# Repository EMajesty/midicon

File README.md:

# MIDI Controller — MCU Pinout and Wiring Reference

MCU: Arduino Mega 2560 Pro  
Logic voltage: 5 V

## 1. MCU Pin Assignments

| Arduino Pin | Net | Function |
|---|---|---|
| D3 | E1_PB | Encoder 1 push button |
| D5 | E1_A | Encoder 1 channel A |
| D7 | E1_B | Encoder 1 channel B |
| D9 | E2_PB | Encoder 2 push button |
| D11 | E2_A | Encoder 2 channel A |
| D14 | E2_B | Encoder 2 channel B |
| D15 | E3_PB | Encoder 3 push button |
| D17 | E3_A | Encoder 3 channel A |
| D18 | MIDI_OUT | MIDI output (TX1) |
| D19 | MIDI_IN | MIDI input (RX1) |
| D21 | E3_B | Encoder 3 channel B |
| D23 | E4_PB | Encoder 4 push button |
| D24 | C1 | Matrix column 1 |
| D25 | E4_A | Encoder 4 channel A |
| D26 | C2 | Matrix column 2 |
| D27 | E4_B | Encoder 4 channel B |
| D28 | C3 | Matrix column 3 |
| D30 | C4 | Matrix column 4 |
| D32 | LEDS | WS2812B data |
| D33 | F1 | Function button 1 |
| D35 | F2 | Function button 2 |
| D36 | LCD_RS | LCD register select |
| D37 | F3 | Function button 3 |
| D38 | LCD_E | LCD enable |
| D39 | F4 | Function button 4 |
| D40 | LCD_DB4 | LCD data bit 4 |
| D41 | R1 | Matrix row 1 |
| D42 | LCD_DB5 | LCD data bit 5 |
| D43 | R2 | Matrix row 2 |
| D44 | LCD_DB6 | LCD data bit 6 |
| D45 | R3 | Matrix row 3 |
| D46 | LCD_DB7 | LCD data bit 7 |
| D47 | R4 | Matrix row 4 |
| A0 | ADC_F1 | Fader 1 |
| A2 | ADC_F2 | Fader 2 |
| A4 | ADC_F3 | Fader 3 |
| A6 | ADC_F4 | Fader 4 |
| A8 | ADC_J1X | Joystick 1 X |
| A10 | ADC_J1Y | Joystick 1 Y |
| A12 | ADC_J2X | Joystick 2 X |
| A14 | ADC_J2Y | Joystick 2 Y |

D0/D1 are reserved for USB serial debugging.

## 2. Rotary Encoders

Four rotary encoders with integrated push buttons.

| Contact | Connection |
|---|---|
| A | E*_A MCU input |
| B | E*_B MCU input |
| Common | GND |
| Push button terminal 1 | E*_PB MCU input |
| Push button terminal 2 | GND |

- All 12 inputs use `INPUT_PULLUP`.
- Rotary contacts pull their respective inputs LOW when closed.
- Push buttons are active LOW.
- Quadrature decoding and debouncing are handled in firmware.

## 3. Function Buttons

Four independent momentary buttons.

| Contact | Connection |
|---|---|
| Terminal 1 | F1–F4 MCU input |
| Terminal 2 | GND |

- Configure as `INPUT_PULLUP`.
- Pressed = LOW.

## 4. Button Matrix

4×4 matrix with one diode per button.

| Row | C1 (D24) | C2 (D26) | C3 (D28) | C4 (D30) |
|---|---|---|---|---|
| R1 (D41) | SW1 | SW2 | SW3 | SW4 |
| R2 (D43) | SW5 | SW6 | SW7 | SW8 |
| R3 (D45) | SW9 | SW10 | SW11 | SW12 |
| R4 (D47) | SW13 | SW14 | SW15 | SW16 |

### Wiring

Each button is wired:

`Column → Switch → Diode anode → Diode cathode → Row`

- Diode cathode (striped end) faces the row.
- One diode per switch prevents ghosting.
- Columns are configured as `INPUT_PULLUP`.
- Scan by driving one row LOW at a time.
- Inactive rows are high-impedance (`INPUT`).
- A pressed button on the active row reads LOW at its column.

## 5. Analog Controls

Four stereo faders (one track used per fader) and two dual-axis joysticks.

| Control | ADC Pin |
|---|---|
| Fader 1 | A0 |
| Fader 2 | A2 |
| Fader 3 | A4 |
| Fader 4 | A6 |
| Joystick 1 X | A8 |
| Joystick 1 Y | A10 |
| Joystick 2 X | A12 |
| Joystick 2 Y | A14 |

### Wiring

Each potentiometer:

| Terminal | Connection |
|---|---|
| End 1 | +5 V |
| Wiper | ADC input |
| End 3 | GND |

- ADC range: 0–1023.
- Reversing the outer terminals reverses the control direction.
- Unused tracks of stereo faders are left unconnected.
- Joystick axes each use one potentiometer.

## 6. WS2812B LEDs

Four addressable RGB LEDs connected in series.

| Signal | Connection |
|---|---|
| First LED DIN | D32 (LEDS) |
| Each LED DOUT | Next LED DIN |
| All VDD | +5 V |
| All VSS | GND |
| Final LED DOUT | Unconnected |

All LEDs are controlled through one MCU pin.

## 7. LCD

20×2 character LCD, 4-bit parallel interface.

Module markings: Winstar WDH0048-TMI-ET#00 / Forewin 2002AE-1.

The following assumes a standard HD44780-compatible 16-pin interface.

| LCD Pin | Signal | Connection |
|---|---|---|
| 1 | VSS | GND |
| 2 | VDD | +5 V |
| 3 | VO | Contrast potentiometer wiper |
| 4 | RS | D36 |
| 5 | R/W | GND |
| 6 | E | D38 |
| 7–10 | DB0–DB3 | Unconnected |
| 11 | DB4 | D40 |
| 12 | DB5 | D42 |
| 13 | DB6 | D44 |
| 14 | DB7 | D46 |
| 15 | LED+ | +5 V (verify current limiting) |
| 16 | LED− | GND |

### Contrast potentiometer (RV9)

| Terminal | Connection |
|---|---|
| End 1 | +5 V |
| Wiper | LCD VO |
| End 3 | GND |

Firmware initialization:

`LiquidCrystal lcd(36, 38, 40, 42, 44, 46);`

## 8. MIDI Input

5-pin DIN MIDI input using a 6N137 optocoupler.

## 9. MIDI Output

5-pin DIN MIDI output driven by hardware UART1.

Firmware:

`Serial1.begin(31250);`

## 10. Power Supply

9 V DC input regulated to 5 V using an L7805.

| Component | Connection |
|---|---|
| Barrel jack positive | +9 V |
| Barrel jack negative | GND |
| L7805 IN | +9 V |
| L7805 GND | GND |
| L7805 OUT | +5 V |
| C2 | Input decoupling |
| C1 | Output decoupling |

The +5 V rail supplies the MCU, controls, LCD, MIDI circuitry and LEDs.

## Firmware and configurator

The v1 firmware is a standalone, four-page configurable MIDI controller. Build it with `pio run -d firmware`; see [firmware/README.md](firmware/README.md) for operation, EEPROM layout, MIDI conventions, and the USB protocol.

The native Python configurator provides JSON validation/import/export, device upload/download, explicit EEPROM save/reload, and a PySide6 GUI:

```sh
python -m pip install -r requirements.txt
python -m configurator validate config/default.json
python -m configurator gui
```

See [configurator/README.md](configurator/README.md) for all commands and [docs/hardware-test-checklist.md](docs/hardware-test-checklist.md) for physical verification.

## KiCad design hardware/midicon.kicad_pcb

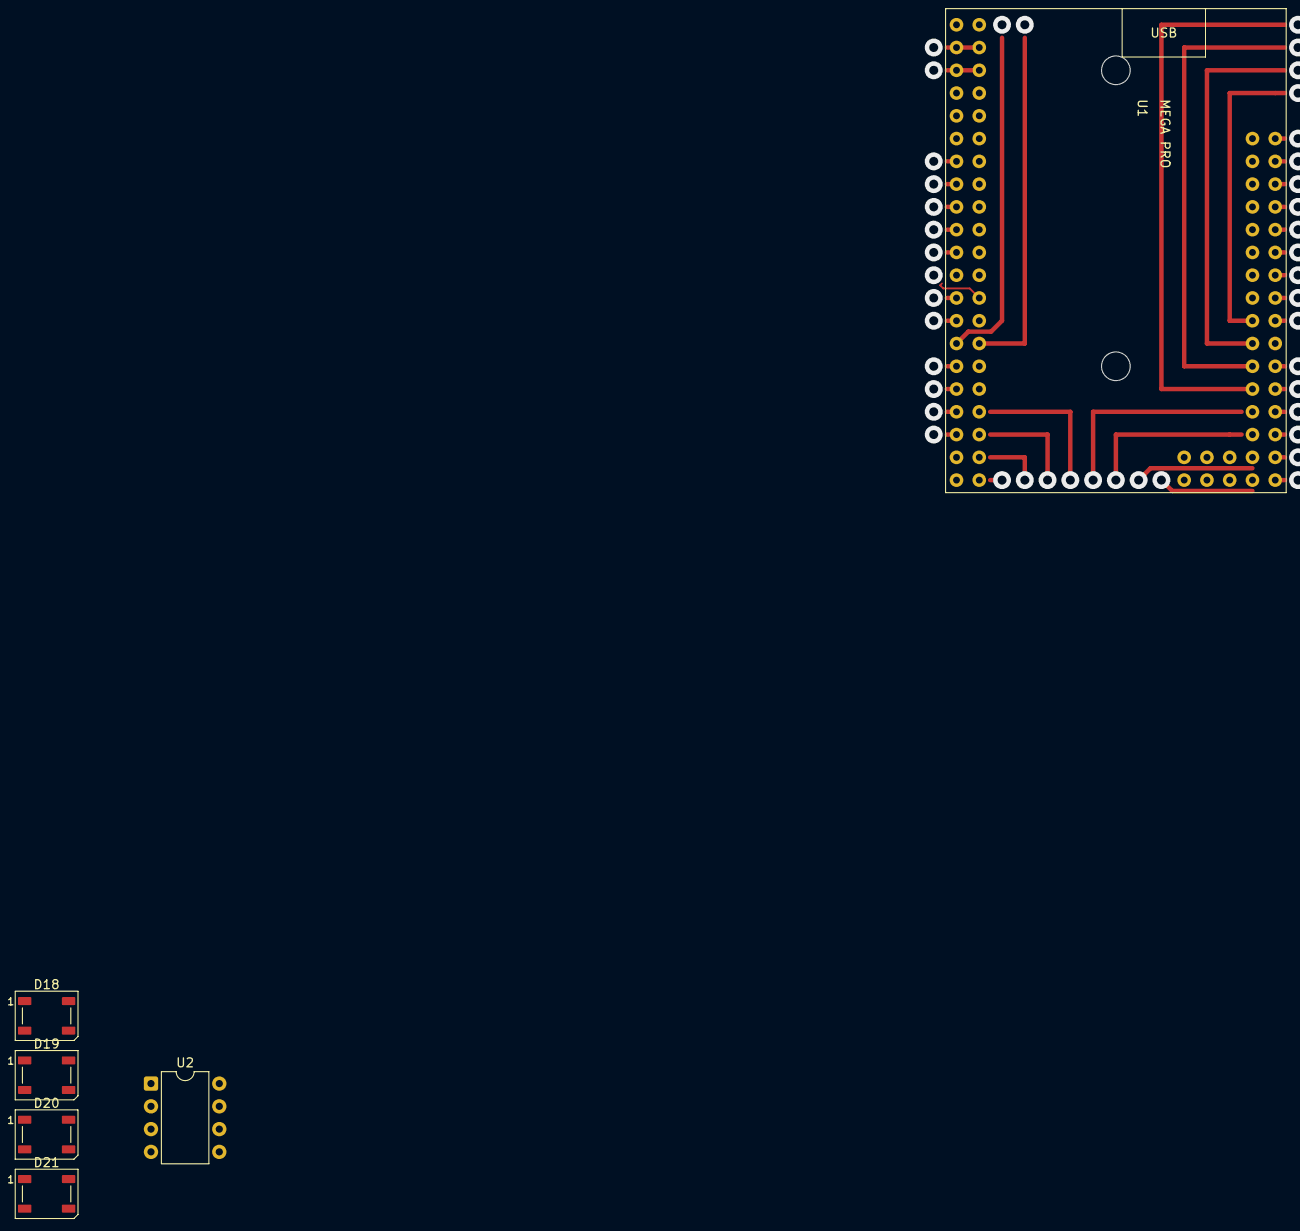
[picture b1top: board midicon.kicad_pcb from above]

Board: 2 copper layers, 6 parts (0 on the bottom side), 7 nets.

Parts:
D18, D19, D20, D21: WS2812B; LED_WS2812B_PLCC4_5.0x5.0mm_P3.2mm
U1: MEGA_2560_PRO; mega2560pro
U2: 6N137; DIP-8_W7.62mm

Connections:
+5V: D18.1 (VDD), D19.1 (VDD), D20.1 (VDD), D21.1 (VDD), U1.43 (5V), U1.44 (5V), U2.8 (VCC)
GND: D18.3 (VSS), D19.3 (VSS), D20.3 (VSS), D21.3 (VSS), U1.41 (GND), U1.42 (GND), U2.5 (GND)
LEDS: D18.4 (DIN), U1.17 (D32)
MIDI_IN: U1.68 (D19), U2.6 (VO)
unnamed: D18.2 (DOUT), D19.4 (DIN)
unnamed: D19.2 (DOUT), D20.4 (DIN)
unnamed: D20.2 (DOUT), D21.4 (DIN)
